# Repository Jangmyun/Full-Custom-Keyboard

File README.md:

# Full-Custom-Keyboard

##### 목표: 아두이노 프로 마이크로 또는 rp2040-zero 보드를 사용하여 스플릿 키보드 제작

###### 저는 전자 비전공자이고, 전기 전자 아무것도 몰라도 무리없이 키보드 제작이 가능했습니다.<br>이 글은 구글링해서 얻은 자료들을 제작 순서에 맞게 짜깁기 한 내용에 불과합니다.

<br><br>

## 순서:

1. #### 레이아웃 설계

2. #### 회로도 설계

3. #### pcb 설계

4. #### 보강판, 상판 설계

5. #### pcb, 부품 주문

6. #### 납땜, qmk 펌웨어 플래시

7. #### 완성

<br><br>

1. ## 레이아웃 설계

#### 키보드 레이아웃 == 키보드 배열

##### 보통 키보드 레이아웃은 키보드 배열을 말하는데, 어떤 배열의 키보드를 만들지 정해야 회로도나 pcb를 설계할 때 고민할 일이 없으니 만들어 놓고 시작하는 것이 좋습니다.<br>키보드 레이아웃은 [keyboard-layout-editor](http://www.keyboard-layout-editor.com/) 에서 만들 수 있습니다.<br>GitHub 계정이 있다면 만든 레이아웃을 저장할 수도 있습니다. JSON 파일로 저장해도 됩니다.

##### 저는 위 배열로 만들겠습니다. fn키를 누르면 나오는 키는 qmk 펌웨어를 사용해서 원하는 대로 어떤 것이든 지정할 수 있으니 나중에 편한대로 커스텀 해도 됩니다.

<br><br><br>

2. ## 회로도 설계

##### 회로도와 PCB는 [KiCad](https://www.kicad.org/) 라는 프로그램을 사용해서 설계할 것입니다. 버전은 7.0 이상의 stable 버전을 기준으로 설명하겠습니다.

<br>

### 회로도 설계전에 알아야 할 내용

#### [키보드 매트릭스 원리 이해하기](https://m.blog.naver.com/kdahaam/221495967863)에 잘 정리되어 있습니다.

##### 

##### 적게는 40키, 많게는 100키가 넘어가는 키보드의 모든 스위치를 하나하나 컨트롤러에 연결하기에 컨트롤러의 핀 개수가 모자르게 됩니다. <br>때문에 행과 열로 스위치를 묶어서 연결하고 각 행과 열을 컨트롤러에 연결하면 훨씬 적은 핀으로 다수의 스위치를 인식할 수 있게 됩니다.<br><br>이렇게 되면 스위치를 하나만 눌렀을 때는 잘 작동하지만 여러 스위치를 동시에 눌렀을 때 눌리지 않은 키까지 인식하는 경우가 생깁니다. 이럴 때 사용하는 것이 `다이오드` 입니다. <br><br>다이오드는 전기를 한 방향으로만 흐르게 만드는 데, 이게 누르지 않은 스위치가 눌리는 현상을 막아줍니다. 잘 이해가 안된다면 `스위치 하나당 다이오드 하나가 필요하다` 정도로 생각하면 되겠습니다. 저는 46개의 스위치를 사용하기 때문에 다이오드 46개가 필요하겠네요.

<br><br>

### 회로도를 설계전에 필요한 파일 설치

#### KiCad를 실행합니다.

##### `Ctrl + n` 또는 New Project를 눌러 새로운 프로젝트를 생성합니다. 프로젝트를 생성했을 때 `프로젝트이름.kicad_pcb`와 `프로젝트이름.kicad_sch`파일을 확인하면 됩니다.

#### Footprint와 Symbol 라이브러리 다운로드

##### Symbol은 우리가 키보드에 사용할 부품의 회로도 그림이고, Footprint는 pcb 설계할 때 사용할 부품의 실제 그림이라고 생각하면 되겠습니다.<br>우리가 사용할 부품을 잘 정리해놓은 [scottoKicad](https://github.com/joe-scotto/scottokeebs/tree/main/Extras/ScottoKicad)가 있습니다. [DownGit](https://minhaskamal.github.io/DownGit/#/home?url=https://github.com/joe-scotto/scottokeebs/tree/main/Extras/ScottoKicad)사이트에서 바로 다운로드 할 수 있습니다.<br>라이브러리 적용 방법은 [KiCad 라이브러리 적용방법](https://github.com/Jangmyun/Full-Custom-Keyboard/tree/main/kicadLibrary)에 정리해두었습니다.

<br><br>

### 본격적으로 회로도를 그려봅시다.

##### 프로젝트 폴더를 열고 `kicad_sch`파일을 열어줍니다.

##### 단축키 `A`를 눌러 스위치와 다이오드 심볼을 추가해주겠습니다. `scottokeebs`로 검색하면 앞서 적용한 심볼 라이브러리를 찾을 수 있습니다.

##### 추가한 스위치와 다이오드를 옮겨서 위와같이 만들어줍니다. 스위치와 다이오드 하나가 세트입니다.<br>이제 앞에서 만든 레이아웃대로 스위치와 다이오드를 배치하겠습니다.<br>스위치와 다이오드를 드래그하고 복사하면 됩니다. 일정한 간격으로 배치해야 와이어를 연결할 때 편리합니다.

##### 어지럽긴 하지만 이런식으로 배치가 됩니다. 저는 스플릿 키보드라서 좌,우 각각 떨어뜨려놨습니다.<br><br>이제 단축키 `W`로 각 행과 열을 연결해주겠습니다.

##### 이런 구조가 되는데, 연결할 때 검은색 원 안의 초록색 점은 서로 연결되었다는 뜻입니다. 연결되지 않은 선 끼리는 빨간색 원처럼 아무것도 표시되지 않습니다. 와이어 교차할 때 주의해야 합니다.

##### 다음은 각 행과 열에 라벨을 붙여줘야 합니다. 같은 이름의 라벨은 PCB 설계 단계에서 서로 연결됩니다.<br>`Ctrl + L`또는 회로도 편집기 우측의 `Global Label`을 선택하고 이름을 정해주면 됩니다.

##### 라벨을 보기쉽게 만드려고 회로도를 조금 수정했습니다. 저는 스플릿 키보드를 만들거라 왼쪽 오른쪽의 라벨 이름을 구분해줬습니다. 보통 행열 라벨은 `col`과 `row`로 작명합니다.

##### 이제 MCU를 회로도에 추가합니다. 스플릿 키보드라서 두개 추가해줍니다. 저는 rp2040-zero를 사용하겠습니다. 단축키 `A`를 누르고 rp2040-zero를 추가합니다.

##### 총 23개의 핀이 있는데 그중에서 `3V3`,`GND`,`5V`외에는 자유롭게 행열을 연결할 수 있습니다. 다만 스플릿 키보드를 만들 때는 좌우 컨트롤러의 시리얼 통신을 위해 `GPIO0`, `GPIO1` 핀을 비워주겠습니다.

##### 연결을 완료했습니다. PCB 설계과정에서 다시 돌아와 수정할 수 있으니 연결되는 위치는 크게 중요하지 않습니다.

### [좌우 컨트롤러의 통신 방법 (스플릿 키보드만 해당)](https://docs.qmk.fm/#/serial_driver?id=usart-full-duplex)

##### MCU의 통신방법은 여러가지가 있는데 우리는 시리얼 통신, 그중에서도 `USART Full-Duplex` 방식을 사용하겠습니다. 이름부터 어려워보이는데 그냥 선 네 개만 잘 연결하면 됩니다.<br>좌우의 연결은 3.5mm 이어폰 잭 (TRRS)로 할겁니다. 따라서 TRRS 커넥터를 추가하겠습니다. `Placeholder_TRRS`로 검색해서 두 개 추가해줍니다.

##### USART Full-Duplex 방식은 TX를 RX에, RX를 TX에 연결해야 합니다. 저는 간단히 TRRS 커넥터의 TX와 RX를 좌우가 엇갈리도록 하겠습니다. 빨간 박스처럼 하면 됩니다.

##### 이제 회로도는 완성됐습니다. PCB파일로 넘어가기 전에 회로도에 들어간 부품들의 실제 Footprint를 지정해줘야 합니다.

##### 에디터 상단의 Footprint Assignment Tool을 열어줍니다.

##### 같은 종류의 부품을 `shift + 마우스클릭`으로 선택해주고 라이브러리에서 부품에 맞는 풋프린트를 더블클릭해주면 적용됩니다.<br>각 심볼에 맞는 풋프린트의 라이브러리와 이름은 다음과 같습니다.

| 심볼          | 라이브러리                  | 풋프린트 이름      |
| ----------- | ---------------------- | ------------ |
| Diode       | ScottoKeebs_Components | Diode_D0-35  |
| Keyswitch   | ScottoKeebs_MX         | MX_PCB_1.00u |
| RP2040_Zero | ScottoKeebs_MCU        | RP2040_Zero  |
| TRRS        | ScottoKeebs_Components | TRRS_PJ-320A |

##### 만약 다른 사이즈의 키캡을 사용한다면 각 사이즈에 맞는 MX스위치 풋프린트를 사용하면 됩니다. 여기까지 하면 회로도는 완성입니다. 이제 PCB 디자인으로 넘어가겠습니다.

<br><br>

3. ## PCB 설계

##### 열려있는 회로도 에디터에서 PCB 에디터를 바로 열어줍니다.

##### 회로도 에디터의 수정사항들을 PCB에 반영합니다.

##### 이제 어지럽게 얽힌 풋프린트들이 에디터에 생깁니다. 서로 연결된 선끼리 이어주면 됩니다. 그 전에 만들고자 하는 키보드의 레이아웃에 맞게 스위치와 다이오드를 정렬해줘야 합니다.

##### 스위치 하나의 가로세로 길이는 `19.05mm`입니다. pcb에디터의 격자 사이즈를 19.05mm를 4로 나눈 `4.7625mm`로 설정하고 진행하겠습니다.

##### User Grid에서 `4.7625mm`로 그리드를 설정해줍니다. 이제 모든 스위치를 예쁘게 정렬하면 됩니다.

##### 기존의 스위치 번호에 유의해서 배치해주면 됩니다. 위치를 중구난방으로 해도 되기는 하는데 나중에 지옥이 펼쳐지니 순서대로 해주세요.

#### 꿀팁:

##### 회로도, pcb에디터 각각 상단의 버튼을 눌러 왔다갔다 할 수 있습니다.<br>이게 왜 좋냐면 회로도 에디터에서 심볼을 선택하면 PCB 에디터에서도 선택된 상태가 됩니다. <br>또 스위치 정렬이 잘 안될 때가 있는데 스위치를 드래그할 때 스위치의 중심부를 잡고 이동하셔야 스위치간 간격이 정확히 맞습니다.

##### 단축키 `S`를 눌러 가장 좌측 상단의 스위치의 좌상단 꼭짓점을 격자의 기준으로 지정합니다.

##### 스위치 정렬이 끝났습니다. 이제 다이오드를 스위치 사이에 끼워넣기 하겠습니다.

##### 다이오드는 PCB 기판의 하단에 넣을겁니다. 다이오드를 전부 선택하고 단축키 `F`를 눌러 뒤집어줍니다. 이제 스위치 사이사이에 다이오드를 배치해줍니다.

##### 스위치의 1/4 지점에 배치해줍니다. 개인적으로 이렇게 배치하는게 행열 연결할 때 깔끔하게 할 수 있어서 좋았습니다.

##### 다이오드 정렬이 끝났습니다. 이제 rp2040-zero와 trrs 커넥터를 배치하고 회로도에 맞춰 선을 연결해주겠습니다.<br>단축키 `X`키로 배선을 시작할 수 있습니다.<br>배선작업을 하기 전에 미리 볼트가 들어갈 구멍을 뚫고 시작해도 됩니다.

#### [KiCAD 사용법 강좌-배선/Copper/비아뚫기 - YouTube](https://youtu.be/5w91CukhzNU?si=pJJ6Ocjb_U-1WQmc)

##### 위 영상에서는 배선 굵기를 조절하는데, 우리는 스위치가 눌린 것만 인식하면 되는 키보드라 따로 조절할 필요는 없습니다. `F.Cu`와 `B.Cu`를 단축키 `V`로 바꿔가면서 배선을 할 수 있습니다.

##### 빨간색이 `F.Cu`고 초록색이 `B.Cu`입니다. 두 선은 각각 앞면, 뒷면의 배선이기 때문에 겹쳐도 합선되지 않습니다. 적절히 섞어가면서 배선작업을 해주면 됩니다.

##### 배선이 완료되었습니다. 저는 여기서 기판을 고정할 볼트가 들어갈 구멍을 뚫어주겠습니다. 다시 회로도 에디터로 돌아갑니다.

##### `Placeeholder_Mounting_Hole`로 검색하고 추가해줍니다.<br>Footprint Assignment Tool을 열어 `MountingHole` 라이브러리의 `MountingHole_2.2mm_M2`를 선택해줍니다. M2 사이즈의 볼트를 사용할겁니다.

##### 다시 PCB 에디터로 돌아와 회로도의 변경사항을 업데이트해줍니다.

##### 나사 체결 홀이 생겼습니다. 이제 이걸 적절한 위치에 배치해주겠습니다.

##### 배치가 완료됐습니다.

#### 이제 기판의 가장자리 커팅라인을 그려줘야 합니다.

##### `Edge.Cuts`를 선택해주고 직선과 호를 그려 PCB의 모양을 잡아주겠습니다.

##### 이런 모양이 됩니다. 왼쪽 오른쪽 따로 만들어도 되는데 주문시 가격이 더 올라가기 때문에 통째로 만들어서 잘라서 사용하는 방식으로 하겠습니다.

#### Design Rules Checker로 잘못된 부분이 있는지 확인해보겠습니다.

##### `Run DRC`버튼을 눌러 확인합니다. `Warnings`에 12개가 나오지만 일단 `Errors`를 중점적으로 체크해주면 됩니다.

##### `Warning`은 대부분 실크스크린(PCB위에 실제로 그려지는 부분)이 잘리면서 생기는 것이 대부분입니다. 크게 신경쓰지 않아도 작동에 이상이 없습니다.

#### 이제 PCB의 나머지 부분을 구리로 채워주겠습니다.

##### 단축키`Ctrl + Shift + Z`나 `Add filled Zone` 버튼을 누르고 에디터의 빈 공간을 클릭해줍니다.<br>레이어를 두개 다 체크 해주고 OK버튼을 누릅니다.

##### PCB 전체를 감싸주고 단축키 `B`키를 눌러 채워줍니다.<br>PCB 디자인의 모든 과정이 끝났습니다. 이제 이 파일을 거버 `.gbr` 파일로 저장해야합니다.

#### [How to generate Gerber and Drill files in KiCad 7](https://jlcpcb.com/help/article/362-how-to-generate-gerber-and-drill-files-in-kicad-7)

##### 위 링크는 우리가 PCB를 주문할 업체인 JLCPCB의 설명문입니다. 그대로 따라해서 거버파일을 한 폴더에 저장하면 됩니다.

###### 수정사항:

###### pcb의 전체적인 디자인과 홀 위치를 수정했습니다.

<br><br>

4. ## 보강판, 하판 설계

##### 이제 보강판, 하판 설계를 해야합니다. 저는 Fusion360 무료버전을 사용해서 만들었습니다.<br>이 부분은 설명하기가 너무 어려워서 잘 만들어진 유튜브 강좌로 대체하겠습니다.<br>진짜 너무 어려워서 설계하기가 힘들다 하시는 분들은 스위치를 고를 때 5핀 스위치를 선택하시고 하판은 최소구매 수량때문에 남는 PCB를 하판으로 이용하면 됩니다. <br>근데 이러면 키보드가 정말 기괴해지니까 저는 보강판을 설계하겠습니다.

[메이커를 위한 Fusion 360 모델링 - YouTube](https://youtube.com/playlist?list=PLovJKdHnVxzlUSWneVlyuwuWpvtWabgab&si=KHW3WNaJRUbpsRhU)

##### 약 2시간 반 정도 강의 따라가면 `.dxf` 형식의 평면 도면 정도는 쉽게 만들 수 있습니다.

##### mx 스위치 상판에는 스위치를 끼울 구멍을 내야하는데, `14mm`로 만들면 됩니다. 저도 아직 툴 사용이 미숙해서 Fusion360 단축키 `D`를 사용해서 길이 노가다를 해줬습니다.

[CherryMX.pdf - Google Drive](https://drive.google.com/file/d/1mCyr-2AKkUAvFVv7urUcg1ZXiUHRZjrM/view)

##### 위 링크는 체리MX 스위치의 상세 스펙입니다. 인치로 표기되어있습니다..

##### 보강판과 하판을 만들어주었습니다. 일단 보강판을 만들면 하판은 거기서 조금만 수정하면 됩니다.

##### 실제로 체결하게 되면 이렇게 됩니다.

[How to save or export a Sketch as DXF in Fusion 360](https://www.autodesk.com/support/technical/article/caas/sfdcarticles/sfdcarticles/How-to-Save-Sketch-as-DXF-in-Fusion-360.html)

##### 만든 도면을 DXF 파일로 저장해줍니다.

<br><br>

5. ## PCB, 부품 주문

##### 이제 PCB와 보강판 설계가 완료됐으니 주문을 해야합니다.

#### PCB:

##### PCB의 경우 [JLCPCB](https://jlcpcb.com/)에서 주문할 수 있습니다.

##### 사이트 회원가입/로그인 후 `Order now`를 누르고 미리 만들어둔 Gerber 파일이 든 폴더를 zip파일로 압축해서 업로드합니다.

##### 파일이 정상이라면 다음처럼 Gerber viewer가 표시됩니다.<br>주문서 아래를 보면 옵션이 매우매우 많은데 우리가 볼 것은 `PCB Color`와 `Surface Finish`뿐입니다. PCB의 색깔은 개인취향에 따라 선택하면 되고 표면마감의 경우 `HASL`과 `ENIG` 방식이 있습니다. 간단히 말하면 `HASL`가 더 싸고, `ENIG`가 마감은 더 좋지만 비쌉니다. 저는 저렴한 HASL로 결정했습니다.<br>결제는 해외결제 카드나 페이팔을 이용하면 됩니다. 아마 처음 회원가입 시 주는 쿠폰이 있을텐데 최대한 이용하는 걸 추천합니다.

##### <br>

#### 보강판:

##### 보강판, 하판은 아크릴로 만들건데, [아트릴](http://www.artryl.com/)이라는 곳을 이용하겠습니다.<br>`제작문의 > 글쓰기`에서 만든 DXF파일을 업로드해주고 원하는 아크릴 색상과 두께를 적어주면 됩니다.<br>저는 상판, 하판 모두 `2t (2mm)`로 했습니다.

<br>

#### 나머지 부품들:

##### [rp2040-zero](https://ko.aliexpress.com/item/1005004281549886.html?spm=a2g0o.productlist.main.1.354e62cbC70N9T&algo_pvid=626a833b-b21b-42ce-b56c-c0ea334f0c61&algo_exp_id=626a833b-b21b-42ce-b56c-c0ea334f0c61-0&pdp_npi=4%40dis%21USD%212.29%211.92%21%21%212.29%21%21%402101fb1717018272371176484eafc5%2112000028615122543%21sea%21KR%21736615590%21&curPageLogUid=QE96GyUpw6MU)

##### [Male-Female/M2x3 & Female-Female/M2x3](https://ko.aliexpress.com/item/1005004564012666.html?spm=a2g0o.cart.0.0.5fbb56baDkGYG4&mp=1&gatewayAdapt=glo2kor)

##### [M2/4mm](https://ko.aliexpress.com/item/1005005070119421.html?spm=a2g0o.cart.0.0.5fbb56baDkGYG4&mp=1&gatewayAdapt=glo2kor)

<br>

##### 제작에 필요한 부품을 모두 구매했습니다. 이제 도착할 때까지 기다리면 됩니다..

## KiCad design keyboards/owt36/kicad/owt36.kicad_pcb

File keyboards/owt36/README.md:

# OWT36

3x5_3 unibody keyboard

+ wireless support
+ MX switch only

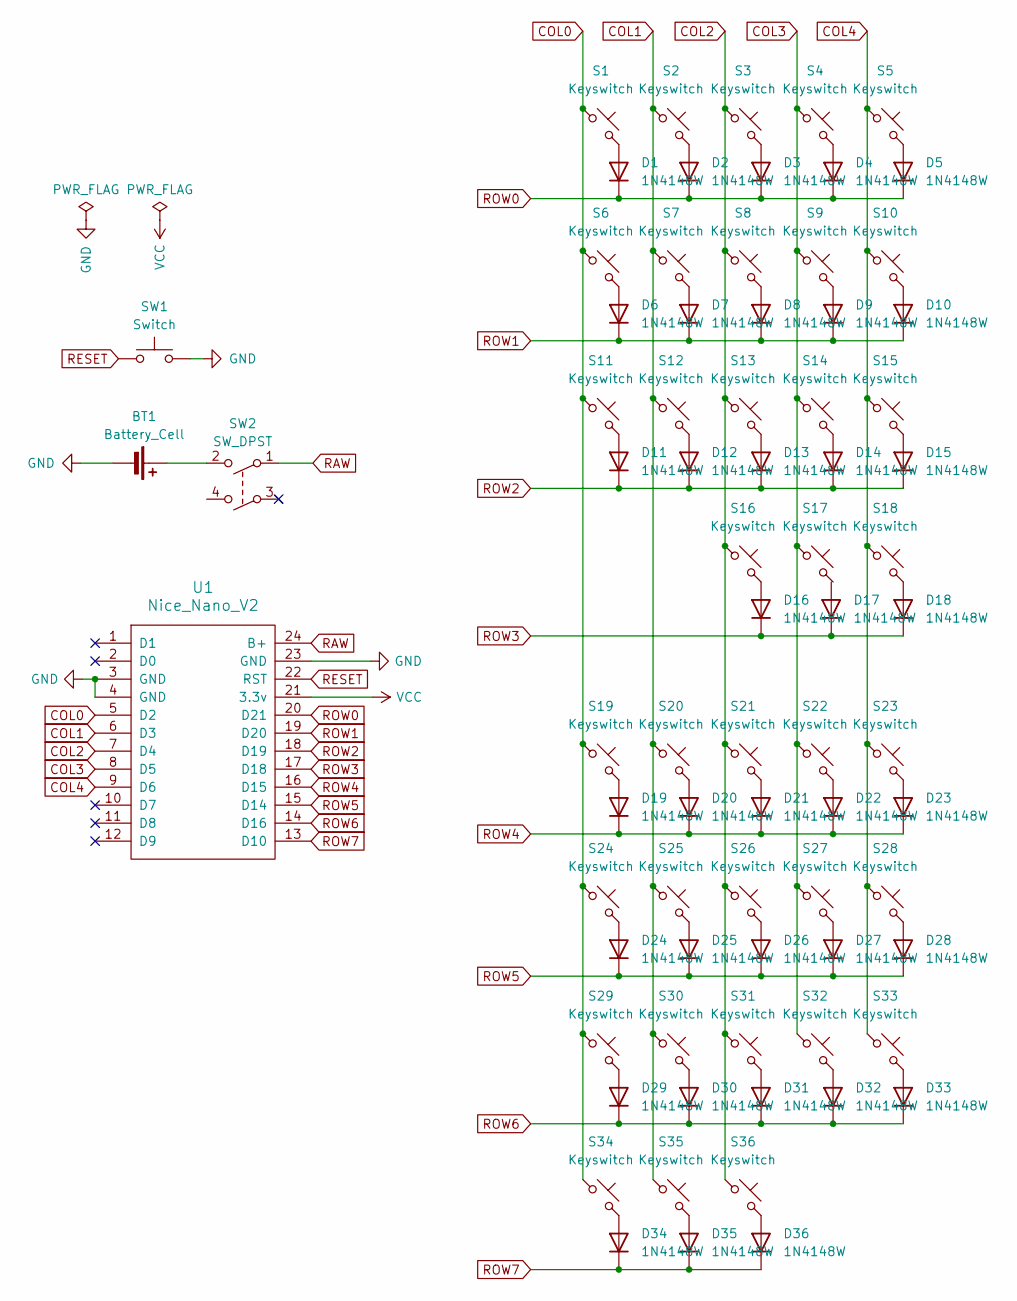
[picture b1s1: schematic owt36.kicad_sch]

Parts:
BT1: Battery_Cell; PinHeader_1x02_P2.00mm_Vertical
D1, D2, D3, D4, D5, D6, D7, D8, D9, D10, D11, D12, D13, D14, D15, D16, D17, D18, D19, D20, D21, D22, D23, D24, D25, D26, D27, D28, D29, D30, D31, D32, D33, D34, D35, D36: 1N4148W; Diode-Hybrid-Back
S1, S2, S3, S4, S5, S6, S7, S8, S9, S10, S11, S12, S13, S14, S15, S16, S17, S18, S19, S20, S21, S22, S23, S24, S25, S26, S27, S28, S29, S30, S31, S32, S33, S34, S35, S36: Keyswitch; Hotswap_MX_1.00u
SW1: Switch; SW_SPST_TL3342
SW2: SW_DPST; SW_SPDT_PCM12
U1: Nice_Nano_V2

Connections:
COL0: S1.1, S6.1, S11.1, S19.1, S24.1, S29.1, S34.1, U1.5 (D2)
COL1: S2.1, S7.1, S12.1, S20.1, S25.1, S30.1, S35.1, U1.6 (D3)
COL2: S3.1, S8.1, S13.1, S16.1, S21.1, S26.1, S31.1, S36.1, U1.7 (D4)
COL3: S4.1, S9.1, S14.1, S17.1, S22.1, S27.1, S32.1, U1.8 (D5)
COL4: S5.1, S10.1, S15.1, S18.1, S23.1, S28.1, S33.1, U1.9 (D6)
GND: BT1.2 (-), SW1.2, U1.3 (GND), U1.4 (GND), U1.23 (GND)
unnamed: BT1.1 (+), SW2.2
unnamed: D1.2 (A), S1.2
unnamed: D2.2 (A), S2.2
unnamed: D3.2 (A), S3.2
unnamed: D4.2 (A), S4.2
unnamed: D5.2 (A), S5.2
unnamed: D6.2 (A), S6.2
unnamed: D7.2 (A), S7.2
unnamed: D8.2 (A), S8.2
unnamed: D9.2 (A), S9.2
unnamed: D10.2 (A), S10.2
unnamed: D11.2 (A), S11.2
unnamed: D12.2 (A), S12.2
unnamed: D13.2 (A), S13.2
unnamed: D14.2 (A), S14.2
unnamed: D15.2 (A), S15.2
unnamed: D16.2 (A), S16.2
unnamed: D18.2 (A), S18.2
unnamed: D19.2 (A), S19.2
unnamed: D20.2 (A), S20.2
unnamed: D21.2 (A), S21.2
unnamed: D22.2 (A), S22.2
unnamed: D23.2 (A), S23.2
unnamed: D24.2 (A), S24.2
unnamed: D25.2 (A), S25.2
unnamed: D26.2 (A), S26.2
unnamed: D27.2 (A), S27.2
unnamed: D28.2 (A), S28.2
unnamed: D29.2 (A), S29.2
unnamed: D30.2 (A), S30.2
unnamed: D31.2 (A), S31.2
unnamed: D32.2 (A), S32.2
unnamed: D33.2 (A), S33.2
unnamed: D34.2 (A), S34.2
unnamed: D35.2 (A), S35.2
unnamed: D36.2 (A), S36.2
RAW: SW2.1, U1.24 (B+)
RESET: SW1.1, U1.22 (RST)
ROW0: D1.1 (K), D2.1 (K), D3.1 (K), D4.1 (K), D5.1 (K), U1.20 (D21)
ROW1: D6.1 (K), D7.1 (K), D8.1 (K), D9.1 (K), D10.1 (K), U1.19 (D20)
ROW2: D11.1 (K), D12.1 (K), D13.1 (K), D14.1 (K), D15.1 (K), U1.18 (D19)
ROW3: D16.1 (K), D17.1 (K), D18.1 (K), U1.17 (D18)
ROW4: D19.1 (K), D20.1 (K), D21.1 (K), D22.1 (K), D23.1 (K), U1.16 (D15)
ROW5: D24.1 (K), D25.1 (K), D26.1 (K), D27.1 (K), D28.1 (K), U1.15 (D14)
ROW6: D29.1 (K), D30.1 (K), D31.1 (K), D32.1 (K), D33.1 (K), U1.14 (D16)
ROW7: D34.1 (K), D35.1 (K), D36.1 (K), U1.13 (D10)
VCC: U1.21 (3.3v)

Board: 2 copper layers, 76 parts (3 on the bottom side), 52 nets, no tracks yet.

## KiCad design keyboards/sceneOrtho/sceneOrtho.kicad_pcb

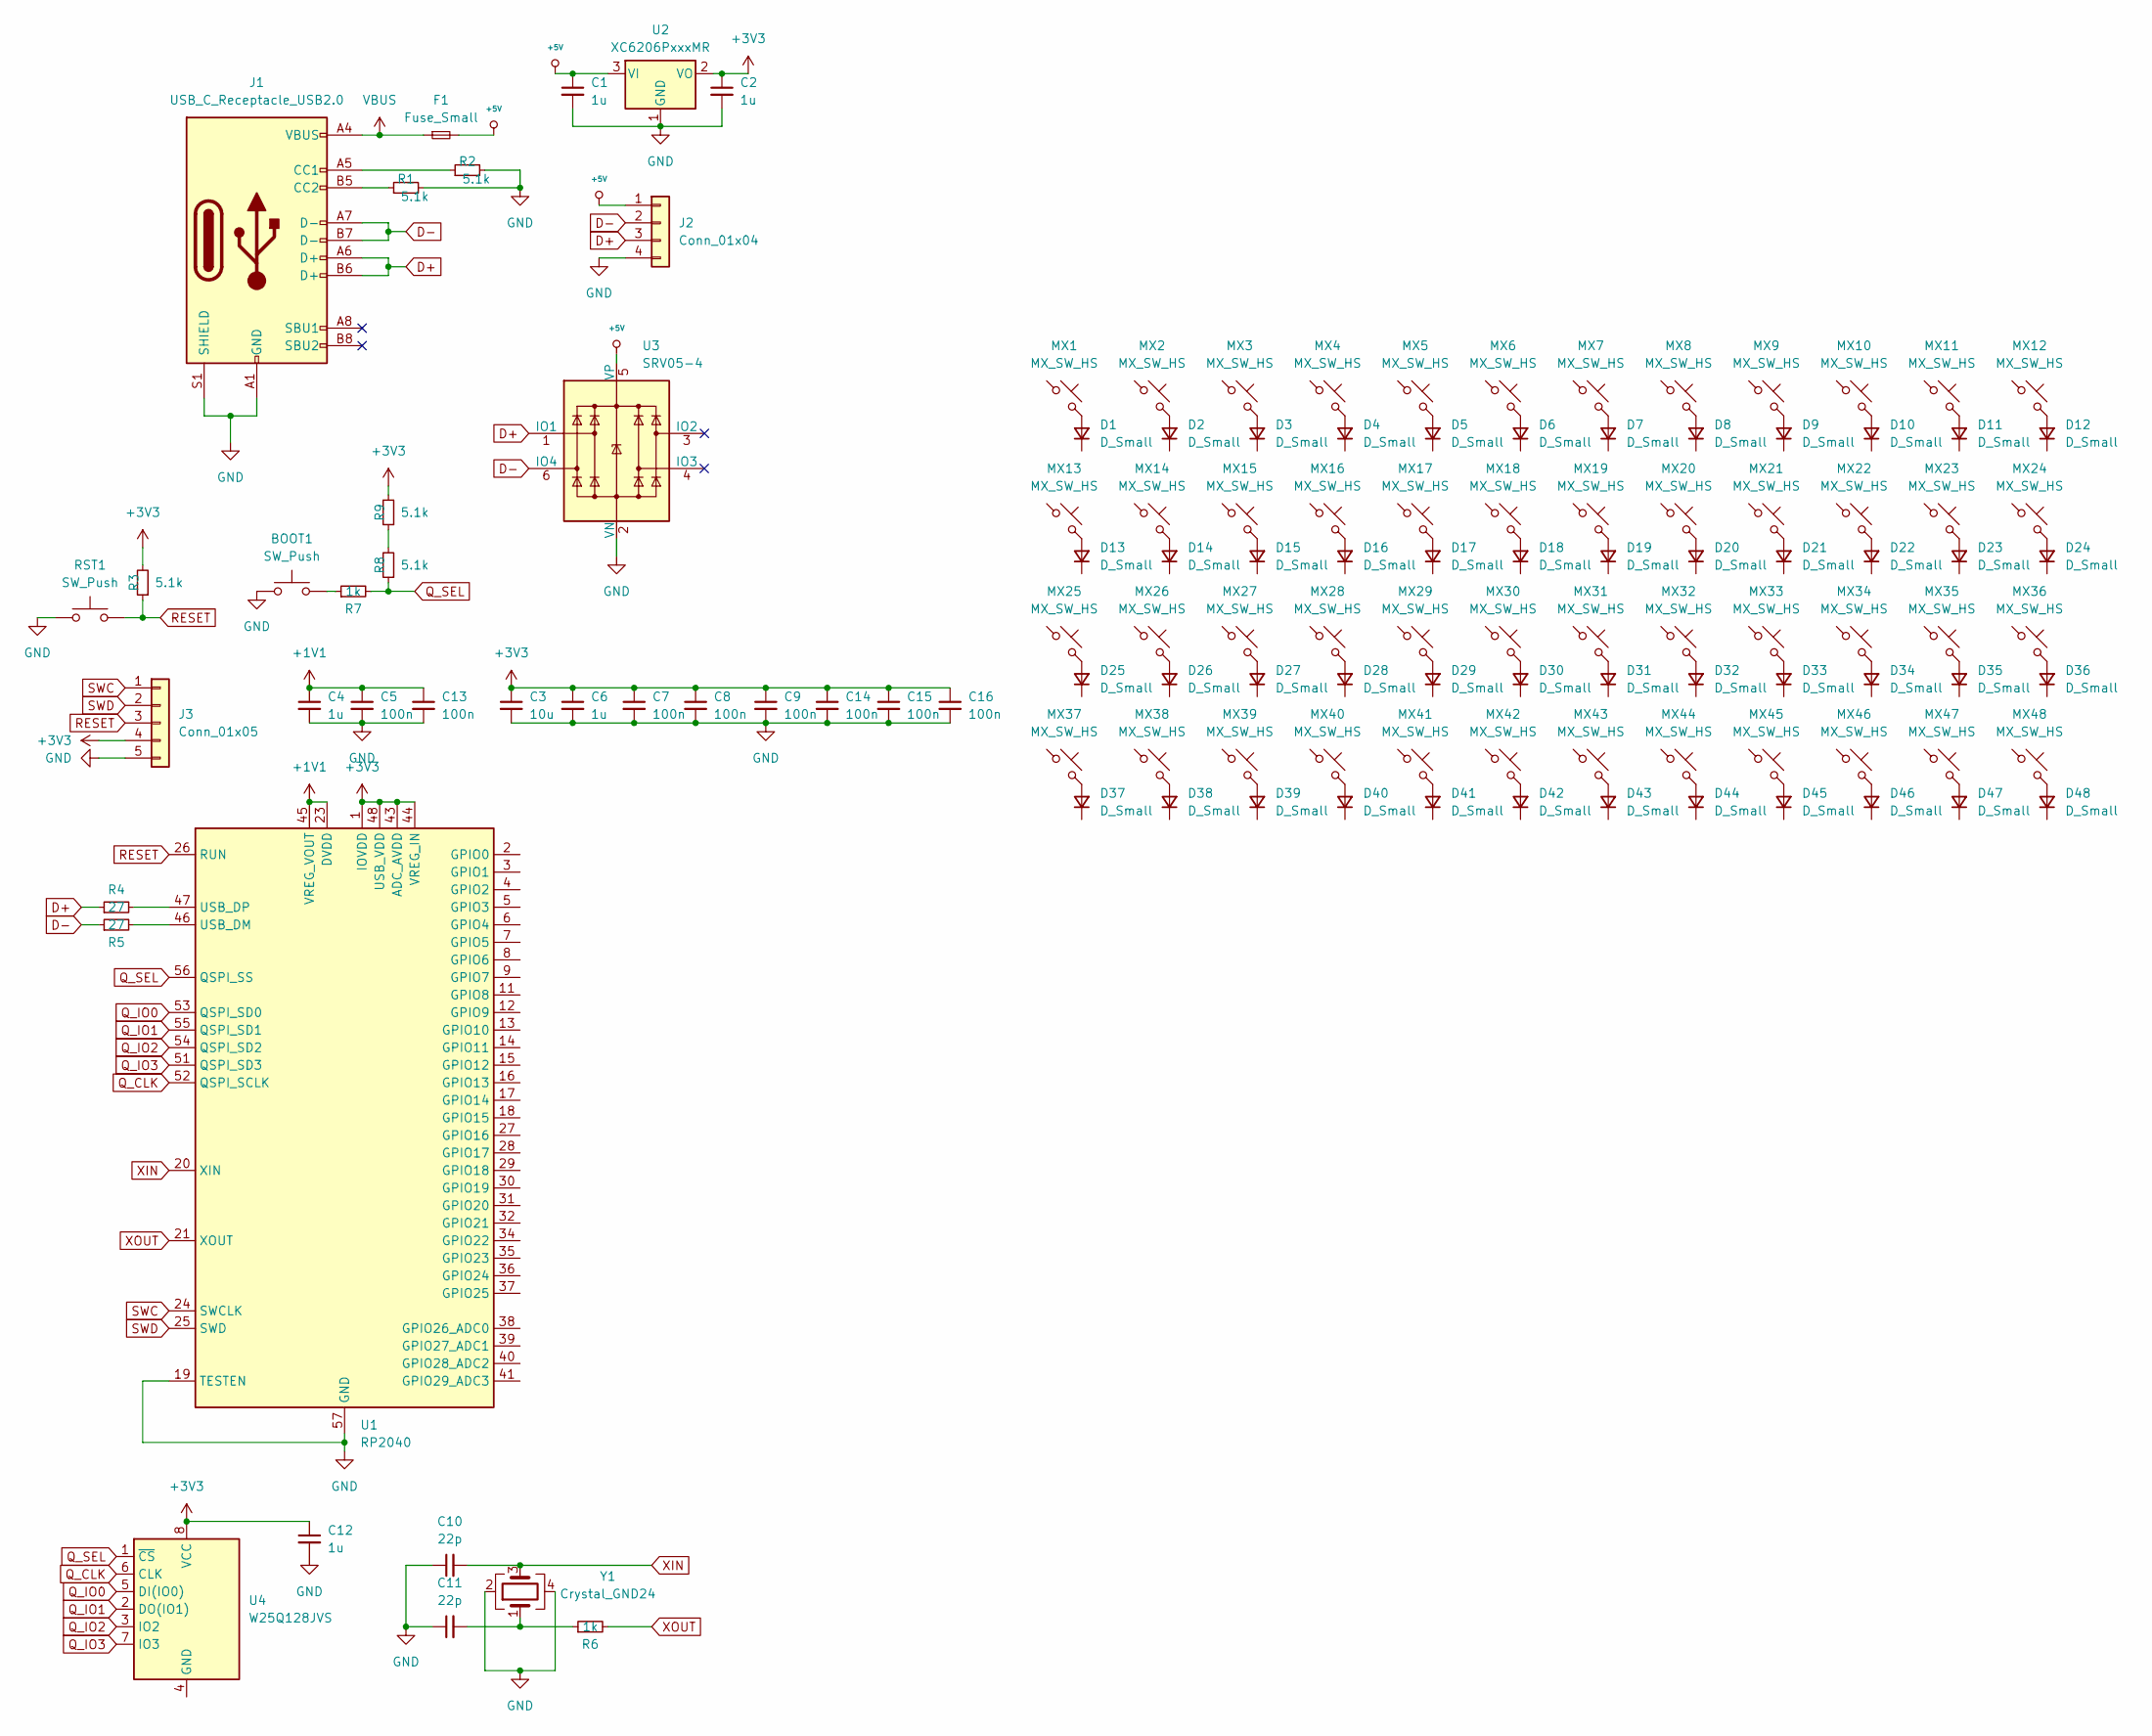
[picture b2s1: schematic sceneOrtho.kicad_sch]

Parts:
BOOT1: SW_Push; SW_SPST_TL3342
C1, C2, C4, C6, C12: 1u; C_0402_1005Metric
C3: 10u; C_0603_1608Metric
C5, C7, C8, C9, C13, C14, C15, C16: 100n; C_0402_1005Metric
C10, C11: 22p; C_0402_1005Metric
D1, D2, D3, D4, D5, D6, D7, D8, D9, D10, D11, D12, D13, D14, D15, D16, D17, D18, D19, D20, D21, D22, D23, D24, D25, D26, D27, D28, D29, D30, D31, D32, D33, D34, D35, D36, D37, D38, D39, D40, D41, D42, D43, D44, D45, D46, D47, D48: D_Small; D_SOD-123
F1: Fuse_Small; Fuse_1206_3216Metric
J1: USB_C_Receptacle_USB2.0; USB_C_Receptacle_HRO_TYPE-C-31-M-12
J2: Conn_01x04; JST_SH_SM04B-SRSS-TB_1x04-1MP_P1.00mm_Horizontal
J3: Conn_01x05; PinHeader_1x05_P2.54mm_Vertical
MX1, MX2, MX3, MX4, MX5, MX6, MX7, MX8, MX9, MX10, MX11, MX12, MX13, MX14, MX15, MX16, MX17, MX18, MX19, MX20, MX21, MX22, MX23, MX24, MX25, MX26, MX27, MX28, MX29, MX30, MX31, MX32, MX33, MX34, MX35, MX36, MX37, MX38, MX39, MX40, MX41, MX42, MX43, MX44, MX45, MX46, MX47, MX48: MX_SW_HS; SW_MX_HS_1u
R1, R2, R3, R8, R9: 5.1k; R_0402_1005Metric
R4, R5: 27; R_0402_1005Metric
R6, R7: 1k; R_0402_1005Metric
RST1: SW_Push; SW_SPST_TL3342
U1: RP2040; QFN-56-1EP_7x7mm_P0.4mm_EP3.2x3.2mm
U2: XC6206PxxxMR; SOT-23-3
U3: SRV05-4; SOT-23-6-routable
U4: W25Q128JVS; SOIC-8_5.23x5.23mm_P1.27mm
Y1: Crystal_GND24; Crystal_SMD_Abracon_ABM3B-4Pin_5.0x3.2mm

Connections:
+1V1: C4.1, C5.1, C13.1, U1.23 (DVDD), U1.45 (VREG_VOUT), U1.50 (DVDD)
+3V3: C2.1, C3.1, C6.1, C7.1, C8.1, C9.1, C12.1, C14.1, C15.1, C16.1, J3.4, R3.2, R9.2, U1.1 (IOVDD), U1.10 (IOVDD), U1.22 (IOVDD), U1.33 (IOVDD), U1.42 (IOVDD), U1.43 (ADC_AVDD), U1.44 (VREG_IN), U1.48 (USB_VDD), U1.49 (IOVDD), U2.2 (VO), U4.8 (VCC)
+5V: C1.1, F1.2, J2.1, U2.3 (VI), U3.5 (VP)
D+: J1.A6 (D+), J1.B6 (D+), J2.3, R4.1, U3.1 (IO1)
D-: J1.A7 (D-), J1.B7 (D-), J2.2, R5.1, U3.6 (IO4)
GND: BOOT1.1, C1.2, C2.2, C3.2, C4.2, C5.2, C6.2, C7.2, C8.2, C9.2, C10.1, C11.1, C12.2, C13.2, C14.2, C15.2, C16.2, J1.A1 (GND), J1.A12 (GND), J1.B1 (GND), J1.B12 (GND), J1.S1 (SHIELD), J2.4, J3.5, R1.2, R2.2, RST1.1, U1.19 (TESTEN), U1.57 (GND), U2.1 (GND), U3.2 (VN), Y1.2, Y1.4
unnamed: BOOT1.2, R7.1
unnamed: C11.2, R6.1, Y1.1
unnamed: D1.2 (A), MX1.2
unnamed: D2.2 (A), MX2.2
unnamed: D3.2 (A), MX3.2
unnamed: D4.2 (A), MX4.2
unnamed: D5.2 (A), MX5.2
unnamed: D6.2 (A), MX6.2
unnamed: D7.2 (A), MX7.2
unnamed: D8.2 (A), MX8.2
unnamed: D9.2 (A), MX9.2
unnamed: D10.2 (A), MX10.2
unnamed: D11.2 (A), MX11.2
unnamed: D12.2 (A), MX12.2
unnamed: D13.2 (A), MX13.2
unnamed: D14.2 (A), MX14.2
unnamed: D15.2 (A), MX15.2
unnamed: D16.2 (A), MX16.2
unnamed: D17.2 (A), MX17.2
unnamed: D18.2 (A), MX18.2
unnamed: D19.2 (A), MX19.2
unnamed: D20.2 (A), MX20.2
unnamed: D21.2 (A), MX21.2
unnamed: D22.2 (A), MX22.2
unnamed: D23.2 (A), MX23.2
unnamed: D24.2 (A), MX24.2
unnamed: D25.2 (A), MX25.2
unnamed: D26.2 (A), MX26.2
unnamed: D27.2 (A), MX27.2
unnamed: D28.2 (A), MX28.2
unnamed: D29.2 (A), MX29.2
unnamed: D30.2 (A), MX30.2
unnamed: D31.2 (A), MX31.2
unnamed: D32.2 (A), MX32.2
unnamed: D33.2 (A), MX33.2
unnamed: D34.2 (A), MX34.2
unnamed: D35.2 (A), MX35.2
unnamed: D36.2 (A), MX36.2
unnamed: D37.2 (A), MX37.2
unnamed: D38.2 (A), MX38.2
unnamed: D39.2 (A), MX39.2
unnamed: D40.2 (A), MX40.2
unnamed: D41.2 (A), MX41.2
unnamed: D42.2 (A), MX42.2
unnamed: D43.2 (A), MX43.2
unnamed: D44.2 (A), MX44.2
unnamed: D45.2 (A), MX45.2
unnamed: D46.2 (A), MX46.2
unnamed: D47.2 (A), MX47.2
unnamed: D48.2 (A), MX48.2
unnamed: J1.A5 (CC1), R2.1
unnamed: J1.B5 (CC2), R1.1
unnamed: R8.2, R9.1
unnamed: R5.2, U1.46 (USB_DM)
unnamed: R4.2, U1.47 (USB_DP)
Q_CLK: U1.52 (QSPI_SCLK), U4.6 (CLK)
Q_IO0: U1.53 (QSPI_SD0), U4.5 (DI(IO0))
Q_IO1: U1.55 (QSPI_SD1), U4.2 (DO(IO1))
Q_IO2: U1.54 (QSPI_SD2), U4.3 (IO2)
Q_IO3: U1.51 (QSPI_SD3), U4.7 (IO3)
Q_SEL: R7.2, R8.1, U1.56 (QSPI_SS), U4.1 (~CS)
RESET: J3.3, R3.1, RST1.2, U1.26 (RUN)
SWC: J3.1, U1.24 (SWCLK)
SWD: J3.2, U1.25 (SWD)
VBUS: F1.1, J1.A4 (VBUS), J1.A9 (VBUS), J1.B4 (VBUS), J1.B9 (VBUS)
XIN: C10.2, U1.20 (XIN), Y1.3
XOUT: R6.2, U1.21 (XOUT)

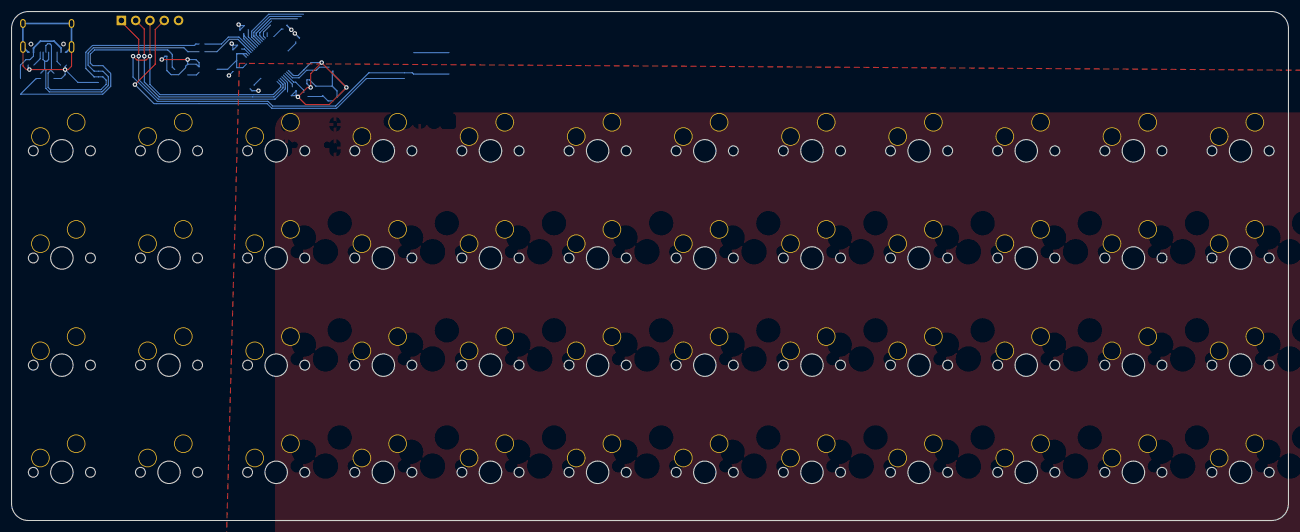
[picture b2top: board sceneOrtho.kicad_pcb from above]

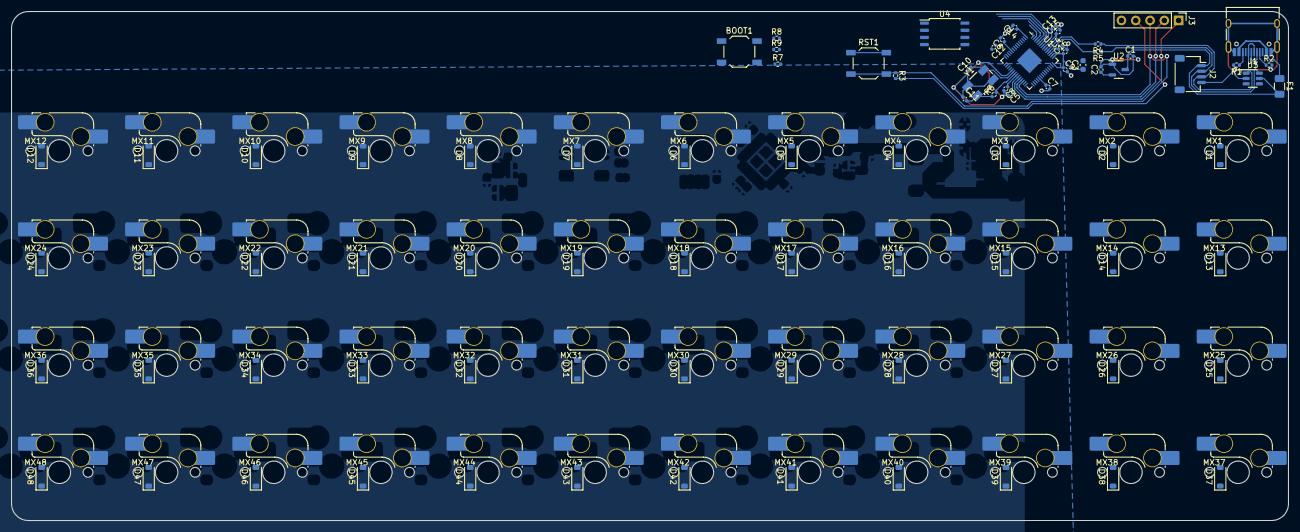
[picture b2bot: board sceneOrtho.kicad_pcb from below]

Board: 2 copper layers, 227.0 x 90.5 mm, 132 parts (132 on the bottom side), 73 nets.

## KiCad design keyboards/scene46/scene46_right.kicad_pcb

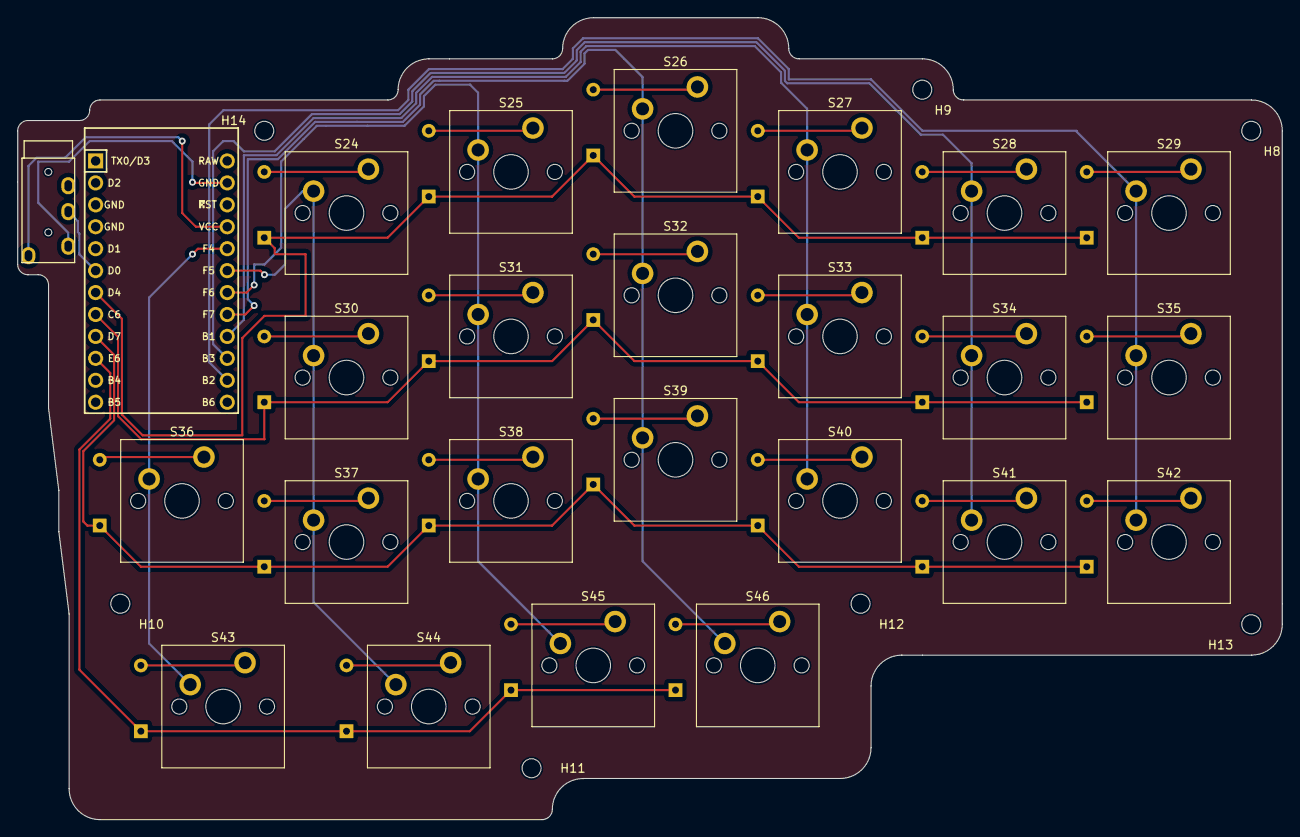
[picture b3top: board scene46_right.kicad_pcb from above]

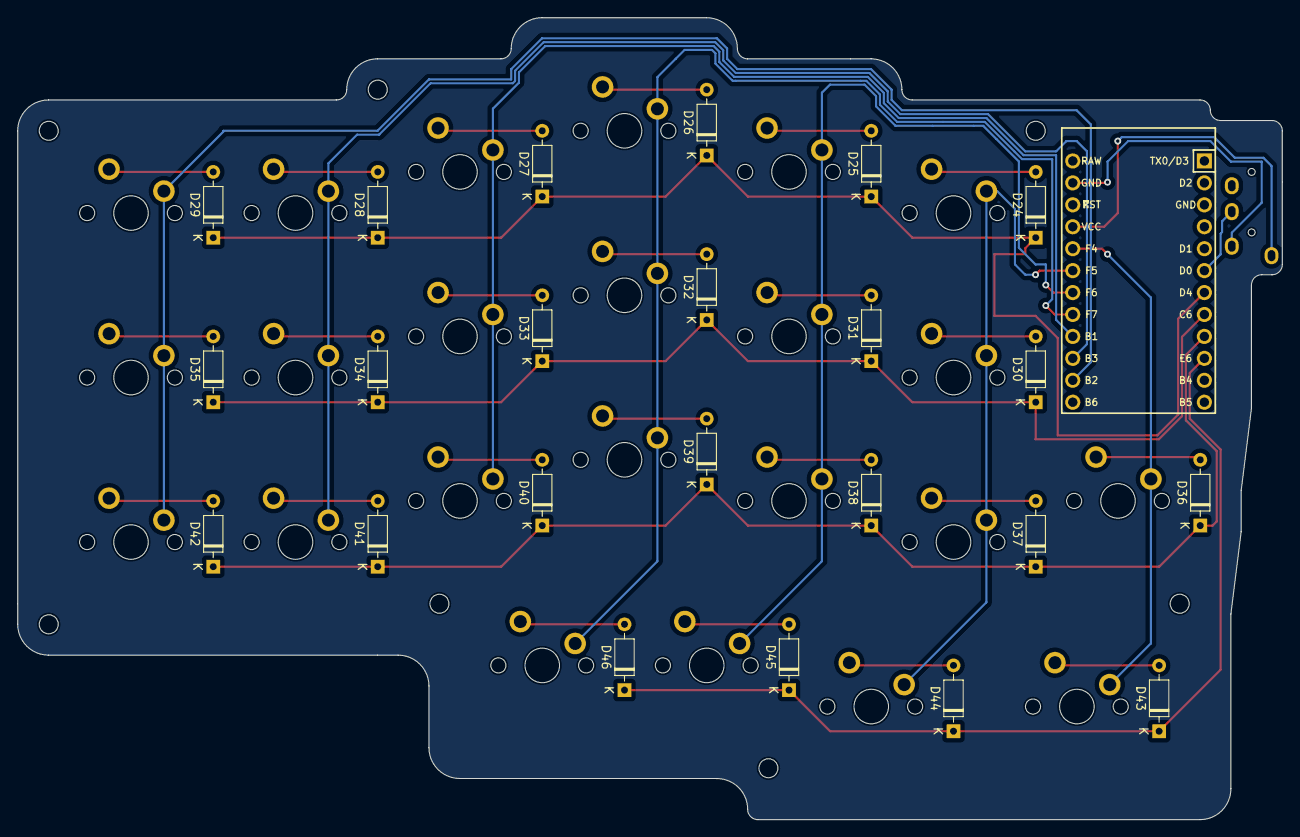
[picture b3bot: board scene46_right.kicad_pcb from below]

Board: 2 copper layers, 146.4 x 92.9 mm, 55 parts (23 on the bottom side), 37 nets.

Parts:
D24, D25, D26, D27, D28, D29, D30, D31, D32, D33, D34, D35, D36, D37, D38, D39, D40, D41, D42, D43, D44, D45, D46: Diode; Diode_DO-35
H8, H9, H10, H11, H12, H13, H14: Mounting_Hole; MountingHole_2.2mm_M2
S24, S25, S26, S27, S28, S29, S30, S31, S32, S33, S34, S35, S36, S37, S38, S39, S40, S41, S42, S44, S45, S46: Keyswitch; MX_PCB_1.00u
S43: Keyswitch; MX_PCB_1.50u
U2: Arduino_Pro_Micro
U4: TRRS; TRRS_PJ-320A

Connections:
GND_R: U2.23 (GND), U4.2 (TIP)
unnamed: D24.2 (A), S24.2
unnamed: D25.2 (A), S25.2
unnamed: D26.2 (A), S26.2
unnamed: D27.2 (A), S27.2
unnamed: D28.2 (A), S28.2
unnamed: D29.2 (A), S29.2
unnamed: D30.2 (A), S30.2
unnamed: D31.2 (A), S31.2
unnamed: D32.2 (A), S32.2
unnamed: D33.2 (A), S33.2
unnamed: D34.2 (A), S34.2
unnamed: D35.2 (A), S35.2
unnamed: D36.2 (A), S36.2
unnamed: D37.2 (A), S37.2
unnamed: D38.2 (A), S38.2
unnamed: D39.2 (A), S39.2
unnamed: D40.2 (A), S40.2
unnamed: D41.2 (A), S41.2
unnamed: D42.2 (A), S42.2
unnamed: D43.2 (A), S43.2
unnamed: D44.2 (A), S44.2
unnamed: D45.2 (A), S45.2
unnamed: D46.2 (A), S46.2
SCL_R: U2.6 (3/PD0), U4.3 (RING1)
VCC_R: U2.21 (VCC), U4.1 (SLEEVE)
col_R0: S36.1, S43.1, U2.20 (A3/PF4)
col_R1: S24.1, S30.1, S37.1, S44.1, U2.19 (A2/PF5)
col_R2: S25.1, S31.1, S38.1, S45.1, U2.18 (A1/PF6)
col_R3: S26.1, S32.1, S39.1, S46.1, U2.17 (A0/PF7)
col_R4: S27.1, S33.1, S40.1, U2.16 (15/PB1)
col_R5: S28.1, S34.1, S41.1, U2.15 (14/PB3)
col_R6: S29.1, S35.1, S42.1, U2.14 (16/PB2)
row_R0: D24.1 (K), D25.1 (K), D26.1 (K), D27.1 (K), D28.1 (K), D29.1 (K), U2.7 (4/PD4)
row_R1: D30.1 (K), D31.1 (K), D32.1 (K), D33.1 (K), D34.1 (K), D35.1 (K), U2.8 (5/PC6)
row_R2: D36.1 (K), D37.1 (K), D38.1 (K), D39.1 (K), D40.1 (K), D41.1 (K), D42.1 (K), U2.9 (6/PD7)
row_R3: D43.1 (K), D44.1 (K), D45.1 (K), D46.1 (K), U2.10 (7/PE6)

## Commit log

2023-11-25 제작한 키보드 업로드
2023-11-25 kiCad 라이브러리 업로드
2023-11-25 add README.md Image
2023-11-26 add keyboard matrix img
2023-11-26 add Kicad Scematic img
2023-11-26 edit footprintSymbol img
2023-11-26 Created New Project
2023-11-26 Add Howt to install kicad libraries
2023-11-26 Add kicad library img
2023-11-26 change img directory
2023-11-26 divide README file
2023-11-26 move img directory
2023-11-26 add img
2023-11-26 add schematic design guide
2023-11-26 add img for schematic design guide
2023-11-28 added backupfiles and contents
2023-11-28 add img for TRRS connection
2023-11-28 add TRRS Connection
2023-11-28 add img for footprint assignment
2023-11-28 add img for pcb design guide
2023-11-28 add pcb design guide
2023-11-28 complete schematic design and edit pcb file
2023-11-29 add PCB routing, Mounting Hole
2023-11-29 add pcb Edge.cuts, Design Rules Checker, and add filled zone
2023-11-29 keyboard pcb design complete
2023-12-05 add switch spec
2023-12-05 comlete pcb editing
2023-12-05 add gerber (.gbr) files
2023-12-05 edit pcb file
2023-12-05 add plate imgs
2023-12-05 add plate design
2023-12-05 pcb edit final
2023-12-05 edit img size
2023-12-06 add new keyboard project
2023-12-10 scene ortho
2023-12-24 new keyboard using rasberry pi pico board
2025-02-01 add owt36 schematic
2025-02-02 readme
2025-02-04 owt36 pcb layout
